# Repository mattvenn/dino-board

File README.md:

# DinoLight

A mosasaurus-shaped light-up circuit board: 20 side-firing addressable LEDs along the spine, a glowing
eye, capacitive touch pads on the bare front face, motion, compass, temperature, light and pressure sensors,
a buzzer, a rechargeable LiPo and USB-C.
The brain is an ESP32-S3 module intended to run CircuitPython. Designed in KiCad 10 for assembly by JLCPCB.

**Status:** work in progress. Read [NOTES.md](NOTES.md) first: it has the current state, every design
decision and its reason, the parts list with stock checks, the review findings, and the pin map.

## What is where

| Path | What it is |
|---|---|
| `NOTES.md` | The running record. Start here |
| `output/schematic.pdf` | The schematic to read (also `schematic_p1..4.png`) |
| `dinolight.kicad_sch`, `mcu.kicad_sch`, `leds.kicad_sch`, `sensors.kicad_sch` | The schematic, generated: do not edit by hand without reading the note below |
| `dinolight.kicad_pcb` | The board, generated from the schematic's netlist and routed by `tools/route_all.sh` |
| `tools/design_spec.py` | Every part and net, declared once. The source of truth |
| `tools/schematic.py` | Draws the schematic from the spec |
| `tools/build_board.py` | Builds the board: outline, placement, nets |
| `tools/route_all.sh` | Builds and routes the board start to finish (calls the tools below) |
| `tools/route_board.py` | Scripted tracks (LED strip, touch lines), autorouter hand-over, ground pours |
| `tools/patch_route.py`, `tools/trim_dangling.py` | Finish what the autorouter leaves open; tie in ground; tidy |
| `tools/freerouting_capped.sh` | Runs the Freerouting autorouter for a set number of passes |
| `routing/route_signals.ses` | The autorouter's last result, kept because it differs run to run |
| `outline/` | The outline generator and its SVG / PNG |
| `lib/` | Project symbols and footprints |
| `datasheets/` | Maker datasheets, named by JLCPCB part number |
| `draft/` | An early quote-only board and its JLCPCB upload files. Not for ordering |

## Regenerating

The schematic and board are written by scripts, so a change is made in `tools/` and the files are
regenerated. Anything edited by hand in KiCad is overwritten the next time a script runs.

```bash
export KICAD_DOCUMENTS_HOME="$PWD/kicad-user"
python3 tools/schematic.py export        # schematic files, PDF and PNGs, and build/sch/netlist.net
tools/route_all.sh                       # the board from that netlist, placed and routed: about 40 minutes
tools/route_all.sh finish                # the same, reusing the saved autorouter result
```

`tools/route_all.sh` needs KiCad 10, Java and Freerouting 2.1.0 at `~/.kicad-mcp/freerouting.jar`. Keep
the computer awake while it runs: the autorouter fails most connections if the machine sleeps part way.
The autorouter's result differs run to run, so check the board the script produces (its last lines
are KiCad's rule-check summary) instead of assuming it matches the last one.

`tools/schematic.py` needs `schdraw.py`, a small drawing library that is not in this repository yet;
`tools/design_spec.py` looks for it in `~/.claude/skills/pcb-for-assembly/scripts`. The board scripts
need KiCad's own Python (for `pcbnew`).

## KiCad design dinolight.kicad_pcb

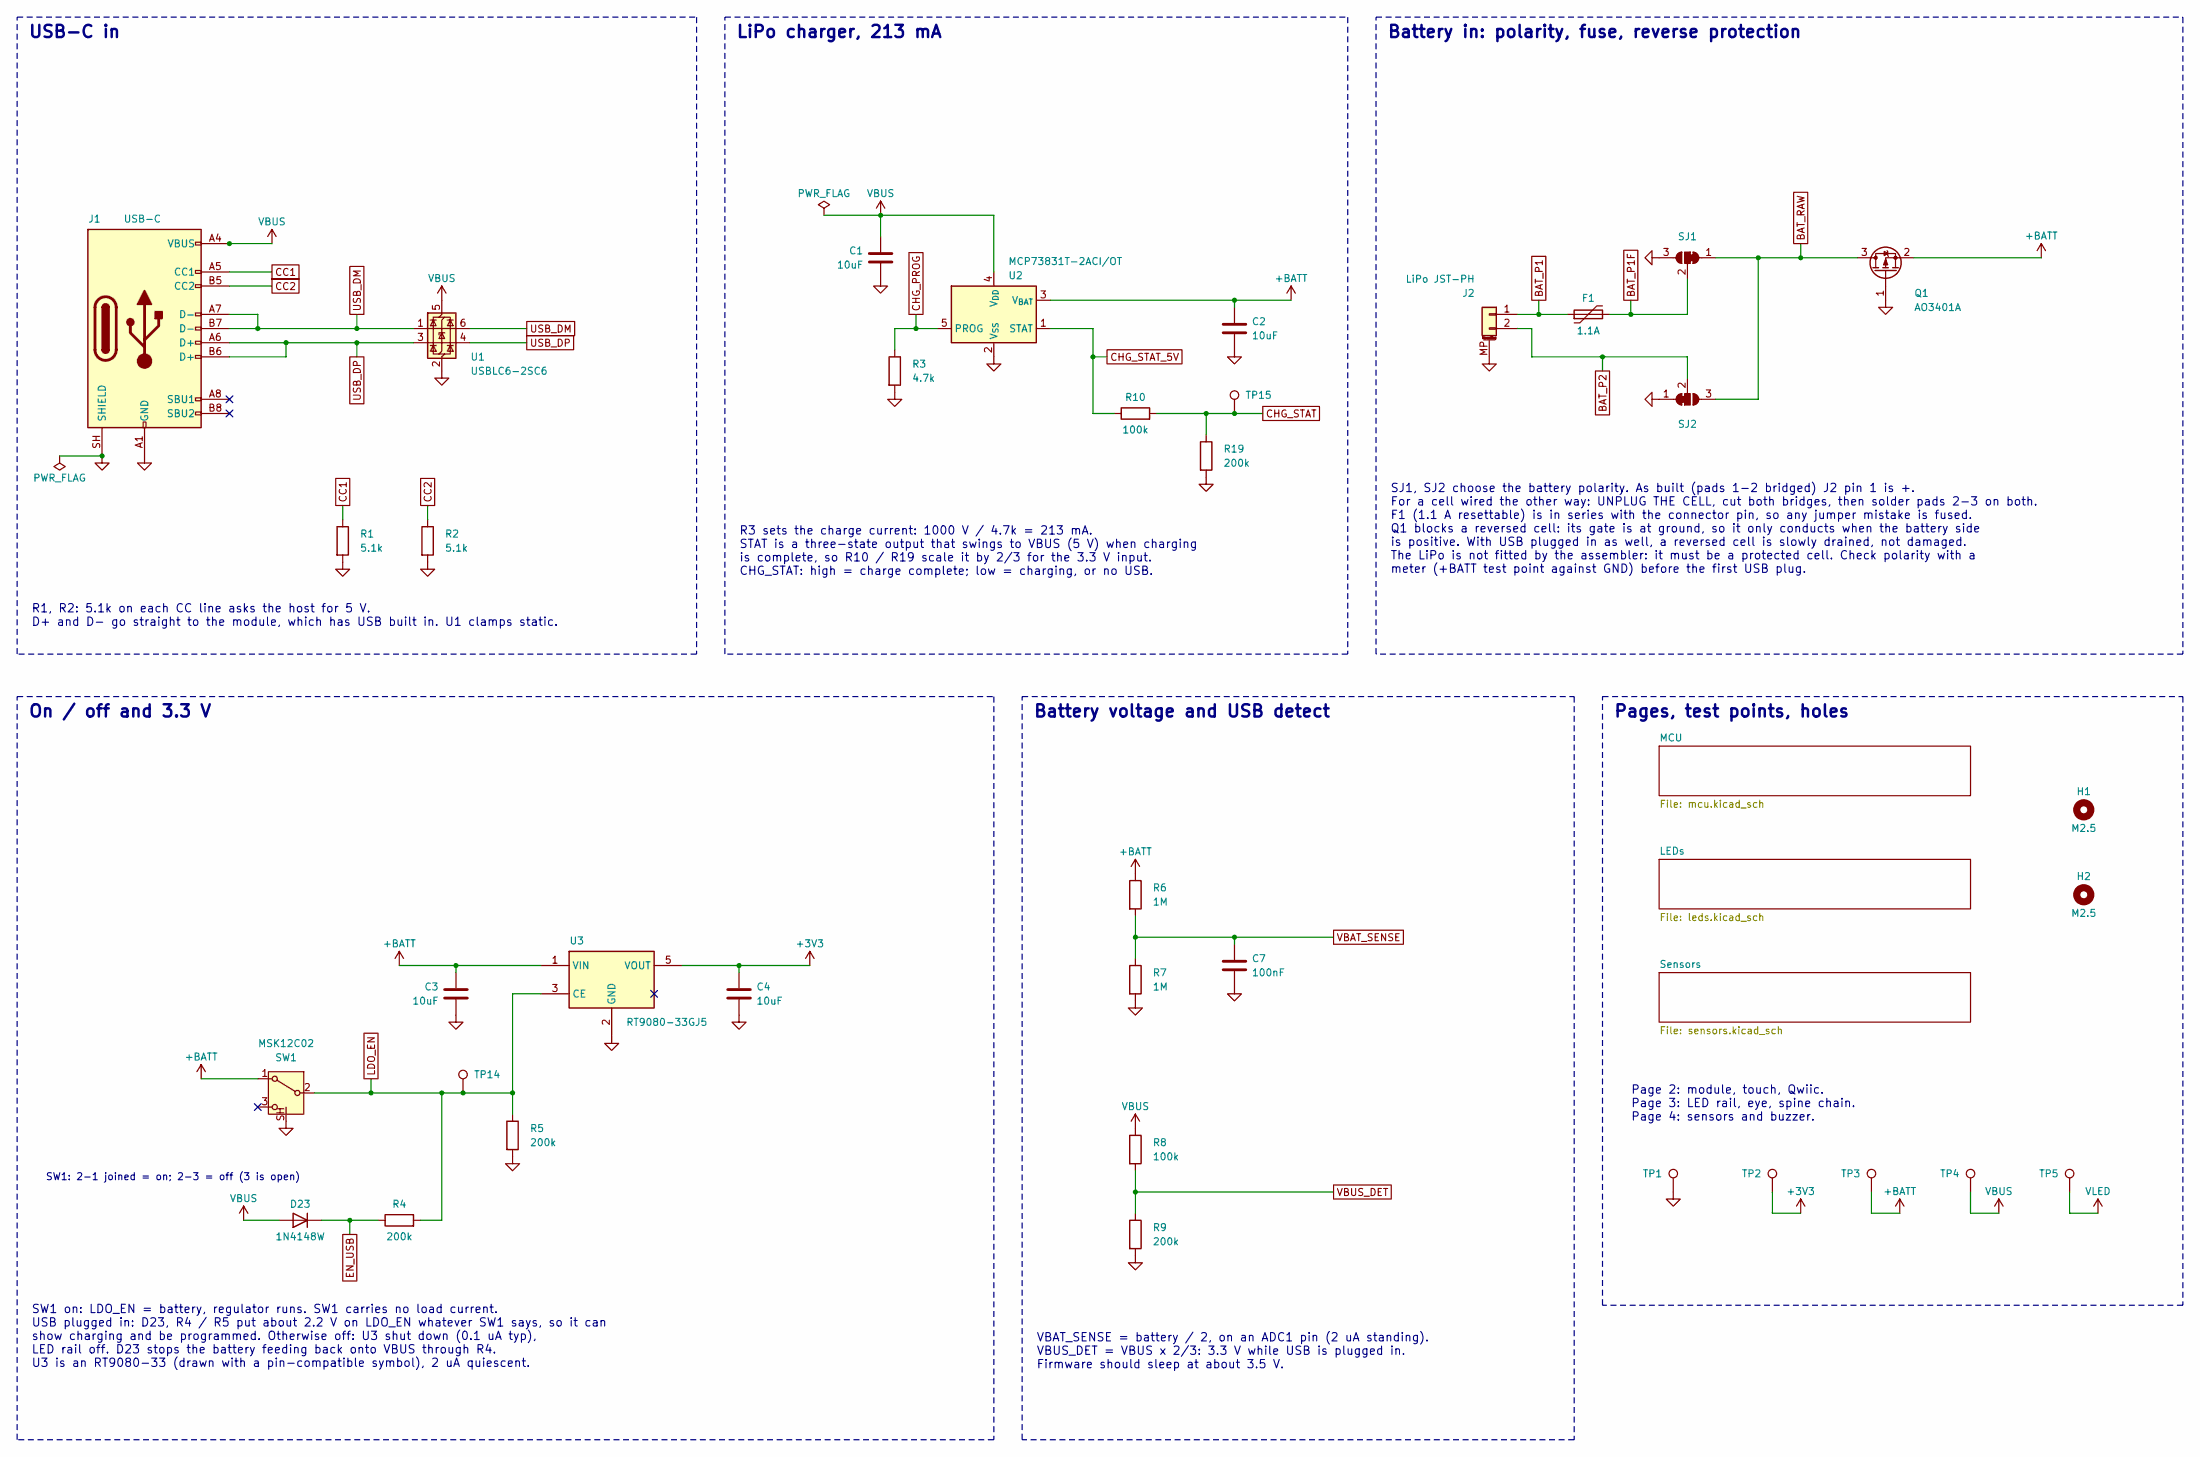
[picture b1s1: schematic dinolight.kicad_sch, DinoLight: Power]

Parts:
C1, C2, C3, C4: 10uF; C_0805_2012Metric; LCSC C15850
C7: 100nF; C_0402_1005Metric; LCSC C1525
D23: 1N4148W; D_SOD-123; LCSC C81598
F1: 1.1A; Fuse_1812_4532Metric; LCSC C21000
H1, H2: M2.5; MountingHole_2.7mm_M2.5
J1: USB-C; USB_C_Receptacle_HRO_TYPE-C-31-M-12; LCSC C165948
J2: LiPo JST-PH; JST_PH_S2B-PH-SM4-TB_1x02-1MP_P2.00mm_Horizontal; LCSC C295747
Q1: AO3401A; SOT-23; LCSC C15127
R1, R2: 5.1k; R_0402_1005Metric; LCSC C25905
R3: 4.7k; R_0402_1005Metric; LCSC C25900
R4, R5, R9, R19: 200k; R_0402_1005Metric; LCSC C25764
R6, R7: 1M; R_0402_1005Metric; LCSC C26083
R8, R10: 100k; R_0402_1005Metric; LCSC C25741
SJ1, SJ2: polarity; SolderJumper-3_P1.3mm_Bridged12_RoundedPad1.0x1.5mm
SW1: MSK12C02; SW_SPDT_Shouhan_MSK12C02; LCSC C431540
TP1: GND; TestPoint_Pad_D1.5mm
TP2: +3V3; TestPoint_Pad_D1.5mm
TP3: +BATT; TestPoint_Pad_D1.5mm
TP4: VBUS; TestPoint_Pad_D1.5mm
TP5: VLED; TestPoint_Pad_D1.5mm
TP14: LDO_EN; TestPoint_Pad_D1.5mm
TP15: CHG_STAT; TestPoint_Pad_D1.5mm
U1: USBLC6-2SC6; SOT-23-6; LCSC C7519
U2: MCP73831T-2ACI/OT; SOT-23-5; LCSC C424093
U3: RT9080-33GJ5; TSOT-23-5; LCSC C841192

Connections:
+3V3: C4.1, TP2.1, U3.5 (VOUT); also elsewhere on the board
+BATT: C2.1, C3.1, Q1.2 (S), R6.1, SW1.1 (A), TP3.1, U2.3 (V_{BAT}), U3.1 (VIN); also elsewhere on the board
BAT_P1: F1.1, J2.1
BAT_P1F: F1.2, SJ1.2 (C)
BAT_P2: J2.2, SJ2.2 (C)
BAT_RAW: Q1.3 (D), SJ1.1 (A), SJ2.3 (B)
CC1: J1.A5 (CC1), R1.1
CC2: J1.B5 (CC2), R2.1
CHG_PROG: R3.1, U2.5 (PROG)
CHG_STAT: R10.2, R19.1, TP15.1; also elsewhere on the board
CHG_STAT_5V: R10.1, U2.1 (STAT)
EN_USB: D23.1 (K), R4.1
GND: C1.2, C2.2, C3.2, C4.2, C7.2, J1.A1 (GND), J1.A12 (GND), J1.B1 (GND), J1.B12 (GND), J1.SH (SHIELD), J2.MP (MountPin), Q1.1 (G), R1.2, R2.2, R3.2, R5.2, R7.2, R9.2, R19.2, SJ1.3 (B), SJ2.1 (A), SW1.SH, TP1.1, U1.2 (GND), U2.2 (V_{SS}), U3.2 (GND); also elsewhere on the board
LDO_EN: R4.2, R5.1, SW1.2 (B), TP14.1, U3.3 (CE)
USB_DM: J1.A7 (D-), J1.B7 (D-), U1.1 (I/O1), U1.6 (I/O1); also elsewhere on the board
USB_DP: J1.A6 (D+), J1.B6 (D+), U1.3 (I/O2), U1.4 (I/O2); also elsewhere on the board
VBAT_SENSE: C7.1, R6.2, R7.1; also elsewhere on the board
VBUS: C1.1, D23.2 (A), J1.A4 (VBUS), J1.A9 (VBUS), J1.B4 (VBUS), J1.B9 (VBUS), R8.1, TP4.1, U1.5 (VBUS), U2.4 (V_{DD})
VBUS_DET: R8.2, R9.1; also elsewhere on the board
VLED: TP5.1; also elsewhere on the board

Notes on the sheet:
USB-C in
R1, R2: 5.1k on each CC line asks the host for 5 V. D+ and D- go straight to the module, which has USB built in. U1 clamps static.
LiPo charger, 213 mA
R3 sets the charge current: 1000 V / 4.7k = 213 mA. STAT is a three-state output that swings to VBUS (5 V) when charging is complete, so R10 / R19 scale it by 2/3 for the 3.3 V input. CHG_STAT: high = charge complete; low = charging, or no USB.
Battery in: polarity, fuse, reverse protection
SJ1, SJ2 choose the battery polarity. As built (pads 1-2 bridged) J2 pin 1 is +. For a cell wired the other way: UNPLUG THE CELL, cut both bridges, then solder pads 2-3 on both. F1 (1.1 A resettable) is in series with the connector pin, so any jumper mistake is fused. Q1 blocks a reversed cell: its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
On / off and 3.3 V
SW1: 2-1 joined = on; 2-3 = off (3 is open)
SW1 on: LDO_EN = battery, regulator runs. SW1 carries no load current. USB plugged in: D23, R4 / R5 put about 2.2 V on LDO_EN whatever SW1 says, so it can show charging and be programmed. Otherwise off: U3 shut down (0.1 uA typ), LED rail off. D23 stops the battery feeding back onto VBUS through R4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
Battery voltage and USB detect
VBAT_SENSE = battery / 2, on an ADC1 pin (2 uA standing). VBUS_DET = VBUS x 2/3: 3.3 V while USB is plugged in. Firmware should sleep at about 3.5 V.
Pages, test points, holes
Page 2: module, touch, Qwiic. Page 3: LED rail, eye, spine chain. Page 4: sensors and buzzer.

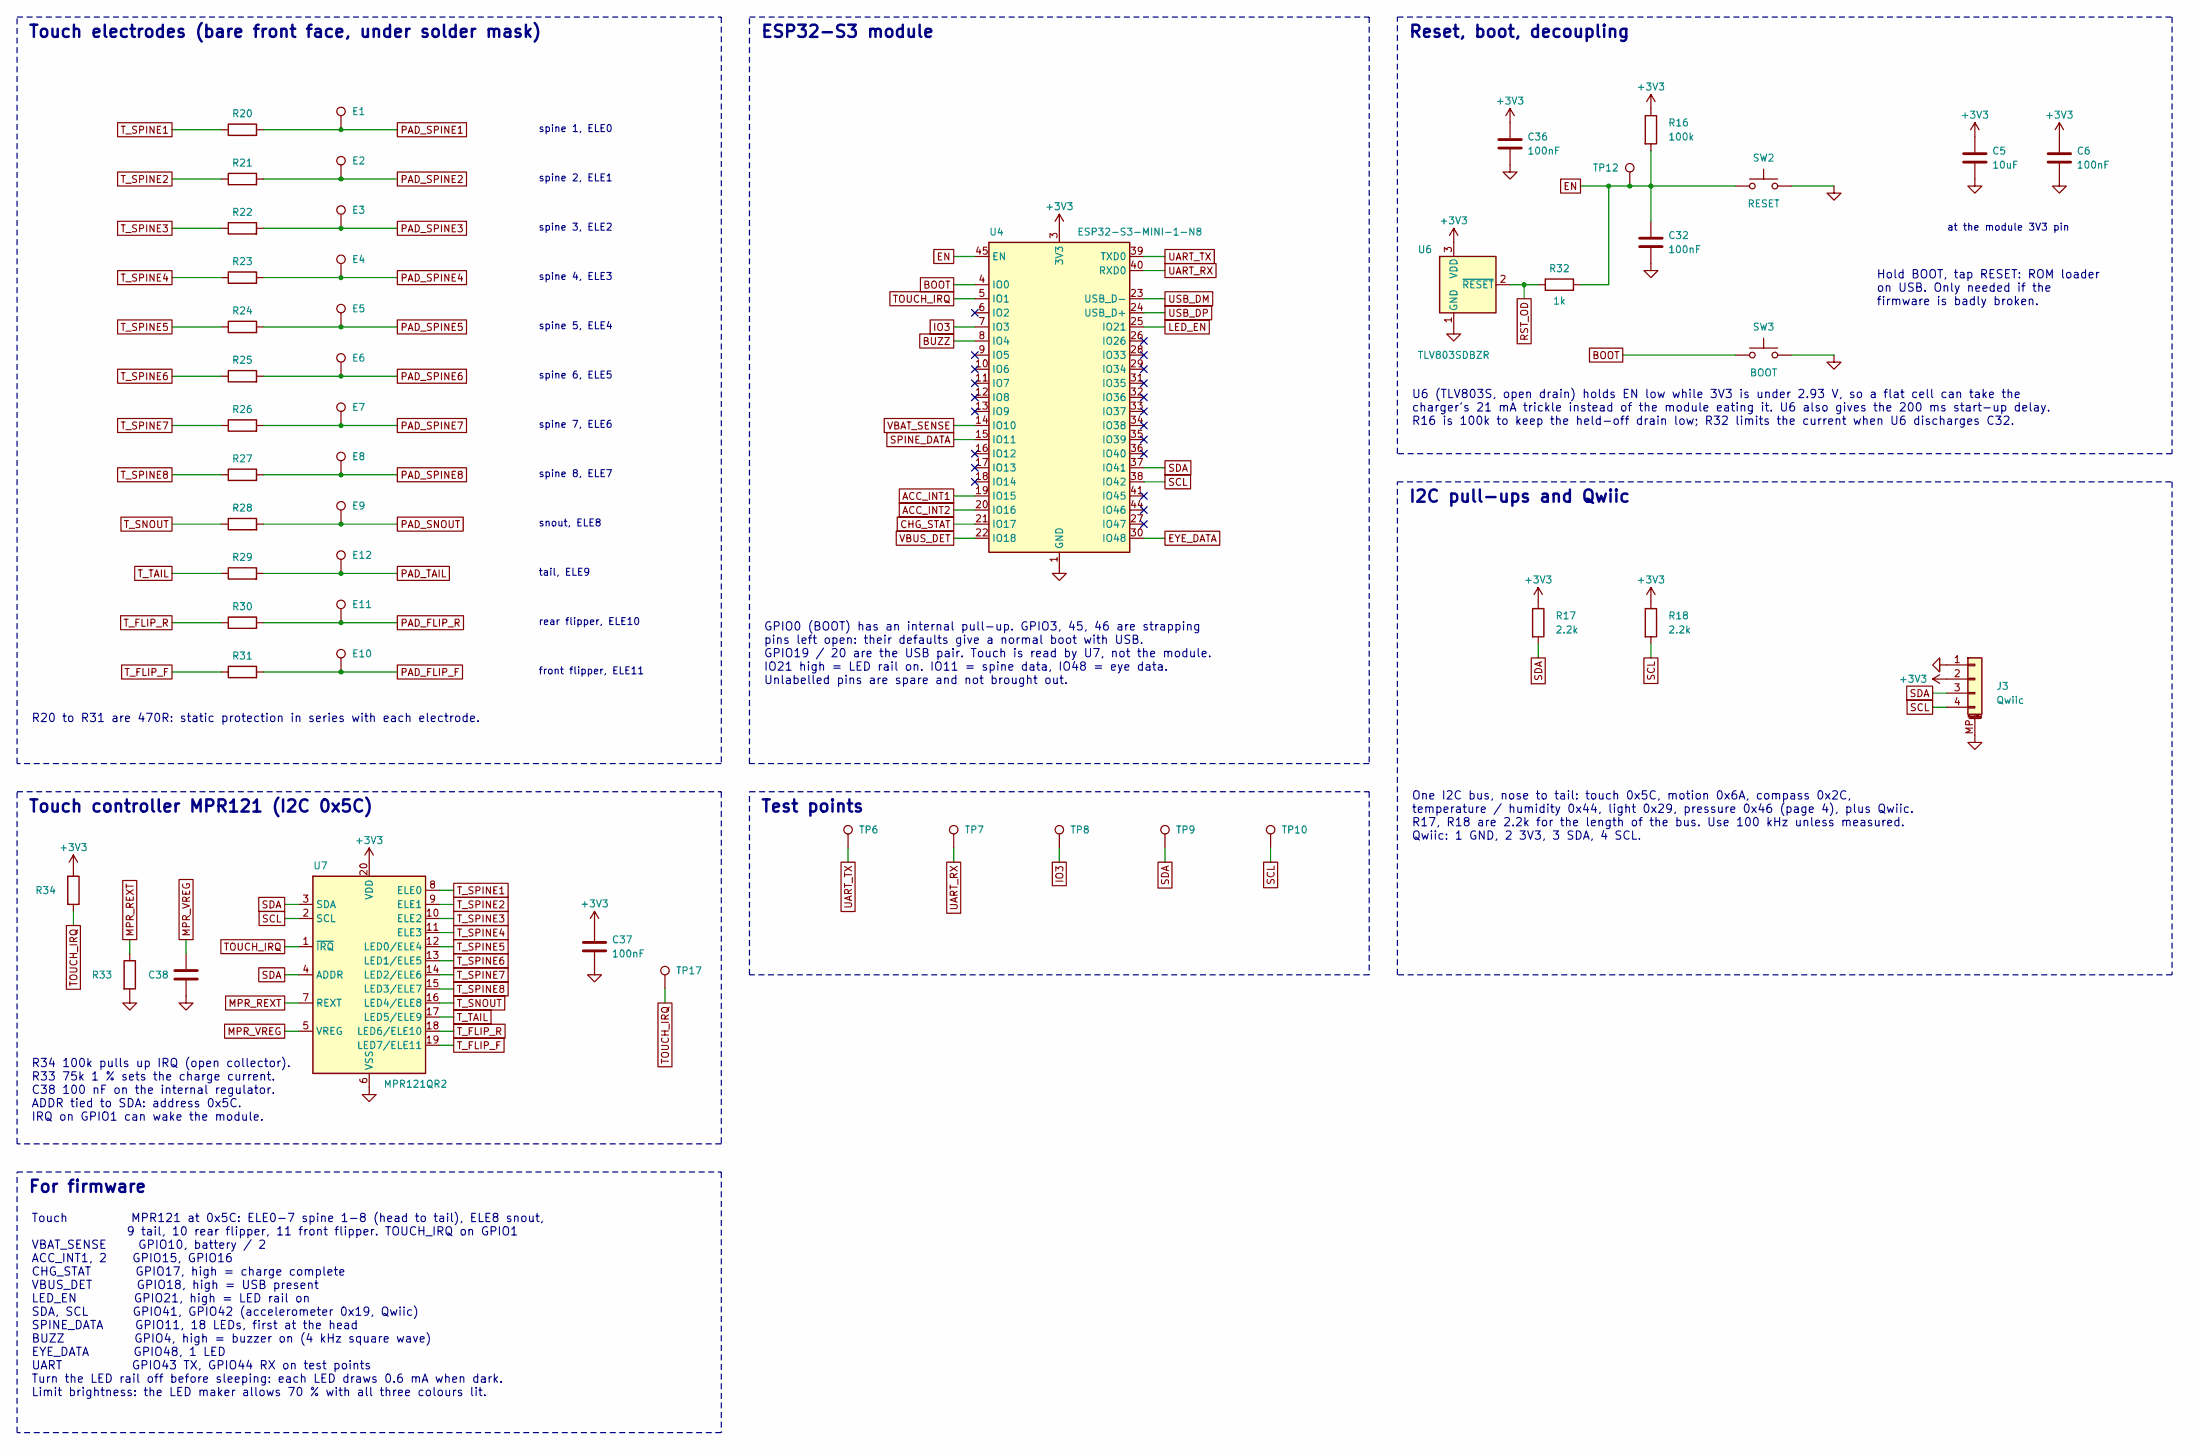
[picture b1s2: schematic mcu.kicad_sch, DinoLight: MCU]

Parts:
C5: 10uF; C_0805_2012Metric; LCSC C15850
C6, C32, C36, C37, C38: 100nF; C_0402_1005Metric; LCSC C1525
E1: spine 1; TouchAnchor
E2: spine 2; TouchAnchor
E3: spine 3; TouchAnchor
E4: spine 4; TouchAnchor
E5: spine 5; TouchAnchor
E6: spine 6; TouchAnchor
E7: spine 7; TouchAnchor
E8: spine 8; TouchAnchor
E9: snout; TouchAnchor
E10: front flipper; TouchAnchor
E11: rear flipper; TouchAnchor
E12: tail; TouchAnchor
J3: Qwiic; JST_SH_SM04B-SRSS-TB_1x04-1MP_P1.00mm_Horizontal; LCSC C160404
R16, R34: 100k; R_0402_1005Metric; LCSC C25741
R17, R18: 2.2k; R_0402_1005Metric; LCSC C25879
R20, R21, R22, R23, R24, R25, R26, R27, R28, R29, R30, R31: 470R; R_0402_1005Metric; LCSC C25117
R32: 1k; R_0402_1005Metric; LCSC C11702
R33: 75k 1%; R_0603_1608Metric; LCSC C23242
SW2: RESET; SW_Push_1P1T_XKB_TS-1187A; LCSC C318884
SW3: BOOT; SW_Push_1P1T_XKB_TS-1187A; LCSC C318884
TP6: UART_TX; TestPoint_Pad_D1.5mm
TP7: UART_RX; TestPoint_Pad_D1.5mm
TP8: IO3; TestPoint_Pad_D1.5mm
TP9: SDA; TestPoint_Pad_D1.5mm
TP10: SCL; TestPoint_Pad_D1.5mm
TP12: EN; TestPoint_Pad_D1.5mm
TP17: TOUCH_IRQ; TestPoint_Pad_D1.5mm
U4: ESP32-S3-MINI-1-N8; ESP32-S2-MINI-1; LCSC C2913206
U6: TLV803SDBZR; SOT-23; LCSC C132016
U7: MPR121QR2; UQFN-20_3x3mm_P0.4mm; LCSC C91322

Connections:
+3V3: C5.1, C6.1, C36.1, C37.1, J3.2, R16.1, R17.1, R18.1, R34.1, U4.3 (3V3), U6.3 (VDD), U7.20 (VDD); also elsewhere on the board
ACC_INT1: U4.19 (IO15); also elsewhere on the board
ACC_INT2: U4.20 (IO16); also elsewhere on the board
BOOT: SW3.1, U4.4 (IO0)
BUZZ: U4.8 (IO4); also elsewhere on the board
CHG_STAT: U4.21 (IO17); also elsewhere on the board
EN: C32.1, R16.2, R32.2, SW2.1, TP12.1, U4.45 (EN)
EYE_DATA: U4.30 (IO48); also elsewhere on the board
GND: C5.2, C6.2, C32.2, C36.2, C37.2, C38.2, J3.1, J3.MP (MountPin), R33.2, SW2.2, SW3.2, U4.1 (GND), U4.2 (GND), U4.42 (GND), U4.43 (GND), U4.46 (GND), U4.47 (GND), U4.48 (GND), U4.49 (GND), U4.50 (GND), U4.51 (GND), U4.52 (GND), U4.53 (GND), U4.54 (GND), U4.55 (GND), U4.56 (GND), U4.57 (GND), U4.58 (GND), U4.59 (GND), U4.60 (GND), U4.61 (GND), U4.62 (GND), U4.63 (GND), U4.64 (GND), U4.65 (GND), U6.1 (GND), U7.6 (VSS); also elsewhere on the board
IO3: TP8.1, U4.7 (IO3)
LED_EN: U4.25 (IO21); also elsewhere on the board
MPR_REXT: R33.1, U7.7 (REXT)
MPR_VREG: C38.1, U7.5 (VREG)
PAD_FLIP_F: E10.1, R31.2
PAD_FLIP_R: E11.1, R30.2
PAD_SNOUT: E9.1, R28.2
PAD_SPINE1: E1.1, R20.2
PAD_SPINE2: E2.1, R21.2
PAD_SPINE3: E3.1, R22.2
PAD_SPINE4: E4.1, R23.2
PAD_SPINE5: E5.1, R24.2
PAD_SPINE6: E6.1, R25.2
PAD_SPINE7: E7.1, R26.2
PAD_SPINE8: E8.1, R27.2
PAD_TAIL: E12.1, R29.2
RST_OD: R32.1, U6.2 (~RESET)
SCL: J3.4, R18.2, TP10.1, U4.38 (IO42), U7.2 (SCL); also elsewhere on the board
SDA: J3.3, R17.2, TP9.1, U4.37 (IO41), U7.3 (SDA), U7.4 (ADDR); also elsewhere on the board
SPINE_DATA: U4.15 (IO11); also elsewhere on the board
TOUCH_IRQ: R34.2, TP17.1, U4.5 (IO1), U7.1 (~IRQ)
T_FLIP_F: R31.1, U7.19 (LED7/ELE11)
T_FLIP_R: R30.1, U7.18 (LED6/ELE10)
T_SNOUT: R28.1, U7.16 (LED4/ELE8)
T_SPINE1: R20.1, U7.8 (ELE0)
T_SPINE2: R21.1, U7.9 (ELE1)
T_SPINE3: R22.1, U7.10 (ELE2)
T_SPINE4: R23.1, U7.11 (ELE3)
T_SPINE5: R24.1, U7.12 (LED0/ELE4)
T_SPINE6: R25.1, U7.13 (LED1/ELE5)
T_SPINE7: R26.1, U7.14 (LED2/ELE6)
T_SPINE8: R27.1, U7.15 (LED3/ELE7)
T_TAIL: R29.1, U7.17 (LED5/ELE9)
UART_RX: TP7.1, U4.40 (RXD0)
UART_TX: TP6.1, U4.39 (TXD0)
USB_DM: U4.23 (USB_D-); also elsewhere on the board
USB_DP: U4.24 (USB_D+); also elsewhere on the board
VBAT_SENSE: U4.14 (IO10); also elsewhere on the board
VBUS_DET: U4.22 (IO18); also elsewhere on the board

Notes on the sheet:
Touch electrodes (bare front face, under solder mask)
spine 1, ELE0
spine 2, ELE1
spine 3, ELE2
spine 4, ELE3
spine 5, ELE4
spine 6, ELE5
spine 7, ELE6
spine 8, ELE7
snout, ELE8
tail, ELE9
rear flipper, ELE10
front flipper, ELE11
R20 to R31 are 470R: static protection in series with each electrode.
Touch controller MPR121 (I2C 0x5C)
R34 100k pulls up IRQ (open collector). R33 75k 1 % sets the charge current. C38 100 nF on the internal regulator. ADDR tied to SDA: address 0x5C. IRQ on GPIO1 can wake the module.
ESP32-S3 module
GPIO0 (BOOT) has an internal pull-up. GPIO3, 45, 46 are strapping pins left open: their defaults give a normal boot with USB. GPIO19 / 20 are the USB pair. Touch is read by U7, not the module. IO21 high = LED rail on. IO11 = spine data, IO48 = eye data. Unlabelled pins are spare and not brought out.
Reset, boot, decoupling
at the module 3V3 pin
Hold BOOT, tap RESET: ROM loader on USB. Only needed if the firmware is badly broken.
U6 (TLV803S, open drain) holds EN low while 3V3 is under 2.93 V, so a flat cell can take the charger's 21 mA trickle instead of the module eating it. U6 also gives the 200 ms start-up delay. R16 is 100k to keep the held-off drain low; R32 limits the current when U6 discharges C32.
I2C pull-ups and Qwiic
One I2C bus, nose to tail: touch 0x5C, motion 0x6A, compass 0x2C, temperature / humidity 0x44, light 0x29, pressure 0x46 (page 4), plus Qwiic. R17, R18 are 2.2k for the length of the bus. Use 100 kHz unless measured. Qwiic: 1 GND, 2 3V3, 3 SDA, 4 SCL.
Test points
For firmware
Touch MPR121 at 0x5C: ELE0-7 spine 1-8 (head to tail), ELE8 snout, 9 tail, 10 rear flipper, 11 front flipper. TOUCH_IRQ on GPIO1 VBAT_SENSE GPIO10, battery / 2 ACC_INT1, 2 GPIO15, GPIO16 CHG_STAT GPIO17, high = charge complete VBUS_DET GPIO18, high = USB present LED_EN GPIO21, high = LED rail on SD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

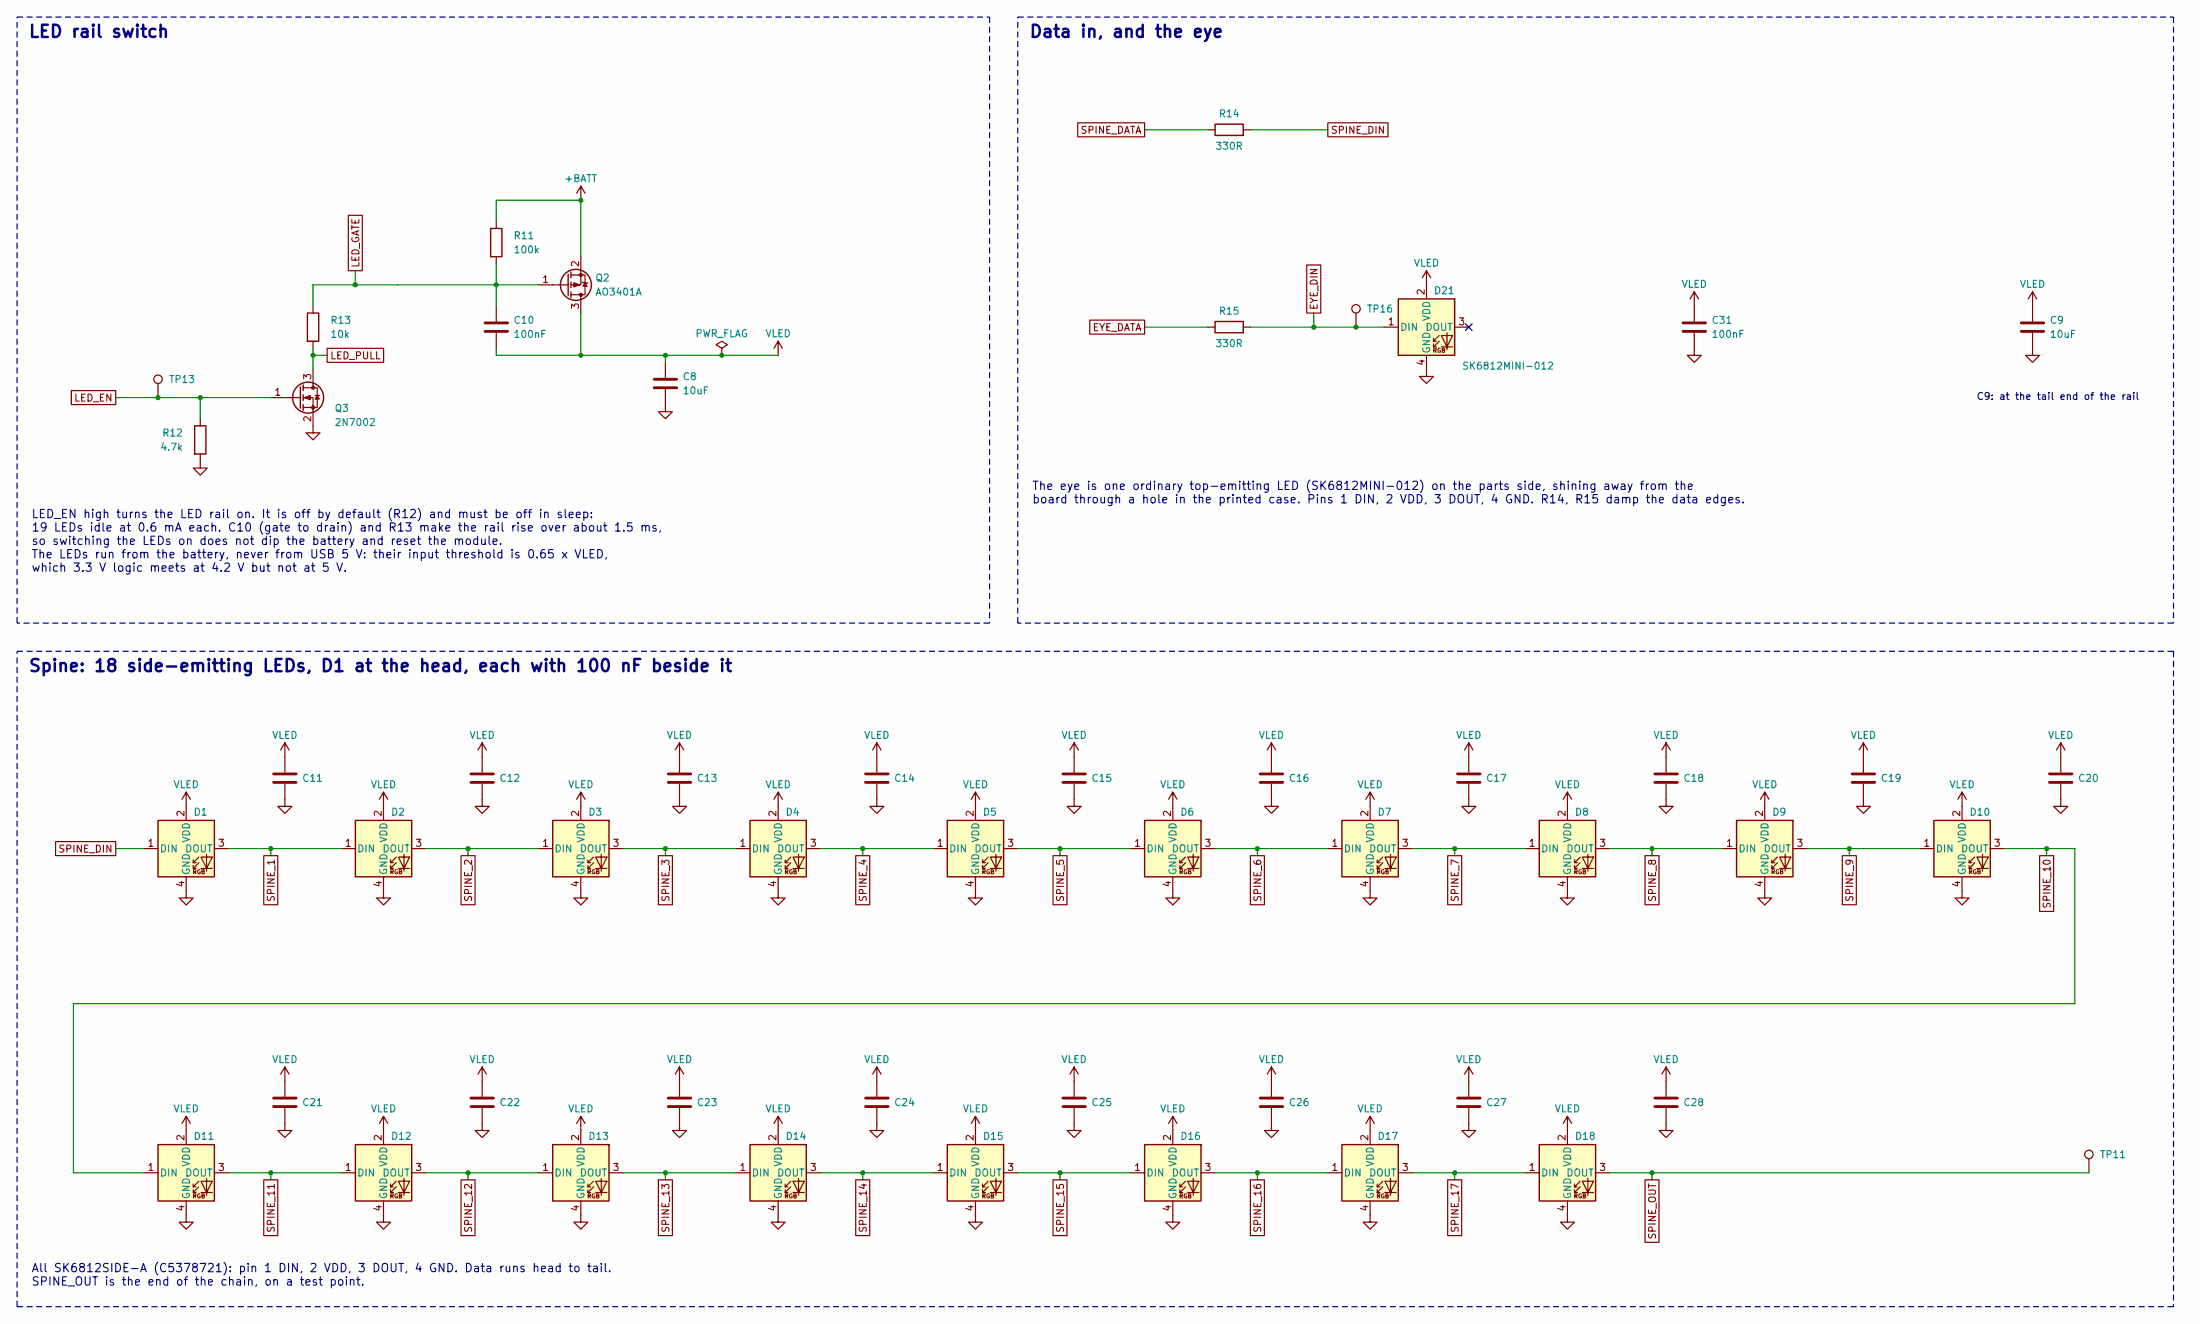
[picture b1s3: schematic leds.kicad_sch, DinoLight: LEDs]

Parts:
C8, C9: 10uF; C_0805_2012Metric; LCSC C15850
C10, C11, C12, C13, C14, C15, C16, C17, C18, C19, C20, C21, C22, C23, C24, C25, C26, C27, C28, C31: 100nF; C_0402_1005Metric; LCSC C1525
D1, D2, D3, D4, D5, D6, D7, D8, D9, D10, D11, D12, D13, D14, D15, D16, D17, D18: SK6812SIDE-A; LED_SK6812SIDE-A_4.0x1.6mm; LCSC C5378721
D21: SK6812MINI-012; LED_SK6812MINI-012_3.7x3.5mm; LCSC C2886570
Q2: AO3401A; SOT-23; LCSC C15127
Q3: 2N7002; SOT-23; LCSC C8545
R11: 100k; R_0402_1005Metric; LCSC C25741
R12: 4.7k; R_0402_1005Metric; LCSC C25900
R13: 10k; R_0402_1005Metric; LCSC C25744
R14, R15: 330R; R_0402_1005Metric; LCSC C25104
TP11: SPINE_OUT; TestPoint_Pad_D1.5mm
TP13: LED_EN; TestPoint_Pad_D1.5mm
TP16: EYE_DIN; TestPoint_Pad_D1.5mm

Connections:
+BATT: Q2.2 (S), R11.1; also elsewhere on the board
EYE_DATA: R15.1; also elsewhere on the board
EYE_DIN: D21.1 (DIN), R15.2, TP16.1
GND: C8.2, C9.2, C11.2, C12.2, C13.2, C14.2, C15.2, C16.2, C17.2, C18.2, C19.2, C20.2, C21.2, C22.2, C23.2, C24.2, C25.2, C26.2, C27.2, C28.2, C31.2, D1.4 (GND), D2.4 (GND), D3.4 (GND), D4.4 (GND), D5.4 (GND), D6.4 (GND), D7.4 (GND), D8.4 (GND), D9.4 (GND), D10.4 (GND), D11.4 (GND), D12.4 (GND), D13.4 (GND), D14.4 (GND), D15.4 (GND), D16.4 (GND), D17.4 (GND), D18.4 (GND), D21.4 (GND), Q3.2 (S), R12.2; also elsewhere on the board
LED_EN: Q3.1 (G), R12.1, TP13.1; also elsewhere on the board
LED_GATE: C10.1, Q2.1 (G), R11.2, R13.1
LED_PULL: Q3.3 (D), R13.2
SPINE_1: D1.3 (DOUT), D2.1 (DIN)
SPINE_2: D2.3 (DOUT), D3.1 (DIN)
SPINE_3: D3.3 (DOUT), D4.1 (DIN)
SPINE_4: D4.3 (DOUT), D5.1 (DIN)
SPINE_5: D5.3 (DOUT), D6.1 (DIN)
SPINE_6: D6.3 (DOUT), D7.1 (DIN)
SPINE_7: D7.3 (DOUT), D8.1 (DIN)
SPINE_8: D8.3 (DOUT), D9.1 (DIN)
SPINE_9: D9.3 (DOUT), D10.1 (DIN)
SPINE_10: D10.3 (DOUT), D11.1 (DIN)
SPINE_11: D11.3 (DOUT), D12.1 (DIN)
SPINE_12: D12.3 (DOUT), D13.1 (DIN)
SPINE_13: D13.3 (DOUT), D14.1 (DIN)
SPINE_14: D14.3 (DOUT), D15.1 (DIN)
SPINE_15: D15.3 (DOUT), D16.1 (DIN)
SPINE_16: D16.3 (DOUT), D17.1 (DIN)
SPINE_17: D17.3 (DOUT), D18.1 (DIN)
SPINE_DATA: R14.1; also elsewhere on the board
SPINE_DIN: D1.1 (DIN), R14.2
SPINE_OUT: D18.3 (DOUT), TP11.1
VLED: C8.1, C9.1, C10.2, C11.1, C12.1, C13.1, C14.1, C15.1, C16.1, C17.1, C18.1, C19.1, C20.1, C21.1, C22.1, C23.1, C24.1, C25.1, C26.1, C27.1, C28.1, C31.1, D1.2 (VDD), D2.2 (VDD), D3.2 (VDD), D4.2 (VDD), D5.2 (VDD), D6.2 (VDD), D7.2 (VDD), D8.2 (VDD), D9.2 (VDD), D10.2 (VDD), D11.2 (VDD), D12.2 (VDD), D13.2 (VDD), D14.2 (VDD), D15.2 (VDD), D16.2 (VDD), D17.2 (VDD), D18.2 (VDD), D21.2 (VDD), Q2.3 (D); also elsewhere on the board

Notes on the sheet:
LED rail switch
LED_EN high turns the LED rail on. It is off by default (R12) and must be off in sleep: 19 LEDs idle at 0.6 mA each. C10 (gate to drain) and R13 make the rail rise over about 1.5 ms, so switching the LEDs on does not dip the battery and reset the module. The LEDs run from the battery, never from US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
Data in, and the eye
C9: at the tail end of the rail
The eye is one ordinary top-emitting LED (SK6812MINI-012) on the parts side, shining away from the board through a hole in the printed case. Pins 1 DIN, 2 VDD, 3 DOUT, 4 GND. R14, R15 damp the data edges.
Spine: 18 side-emitting LEDs, D1 at the head, each with 100 nF beside it
All SK6812SIDE-A (C5378721): pin 1 DIN, 2 VDD, 3 DOUT, 4 GND. Data runs head to tail. SPINE_OUT is the end of the chain, on a test point.

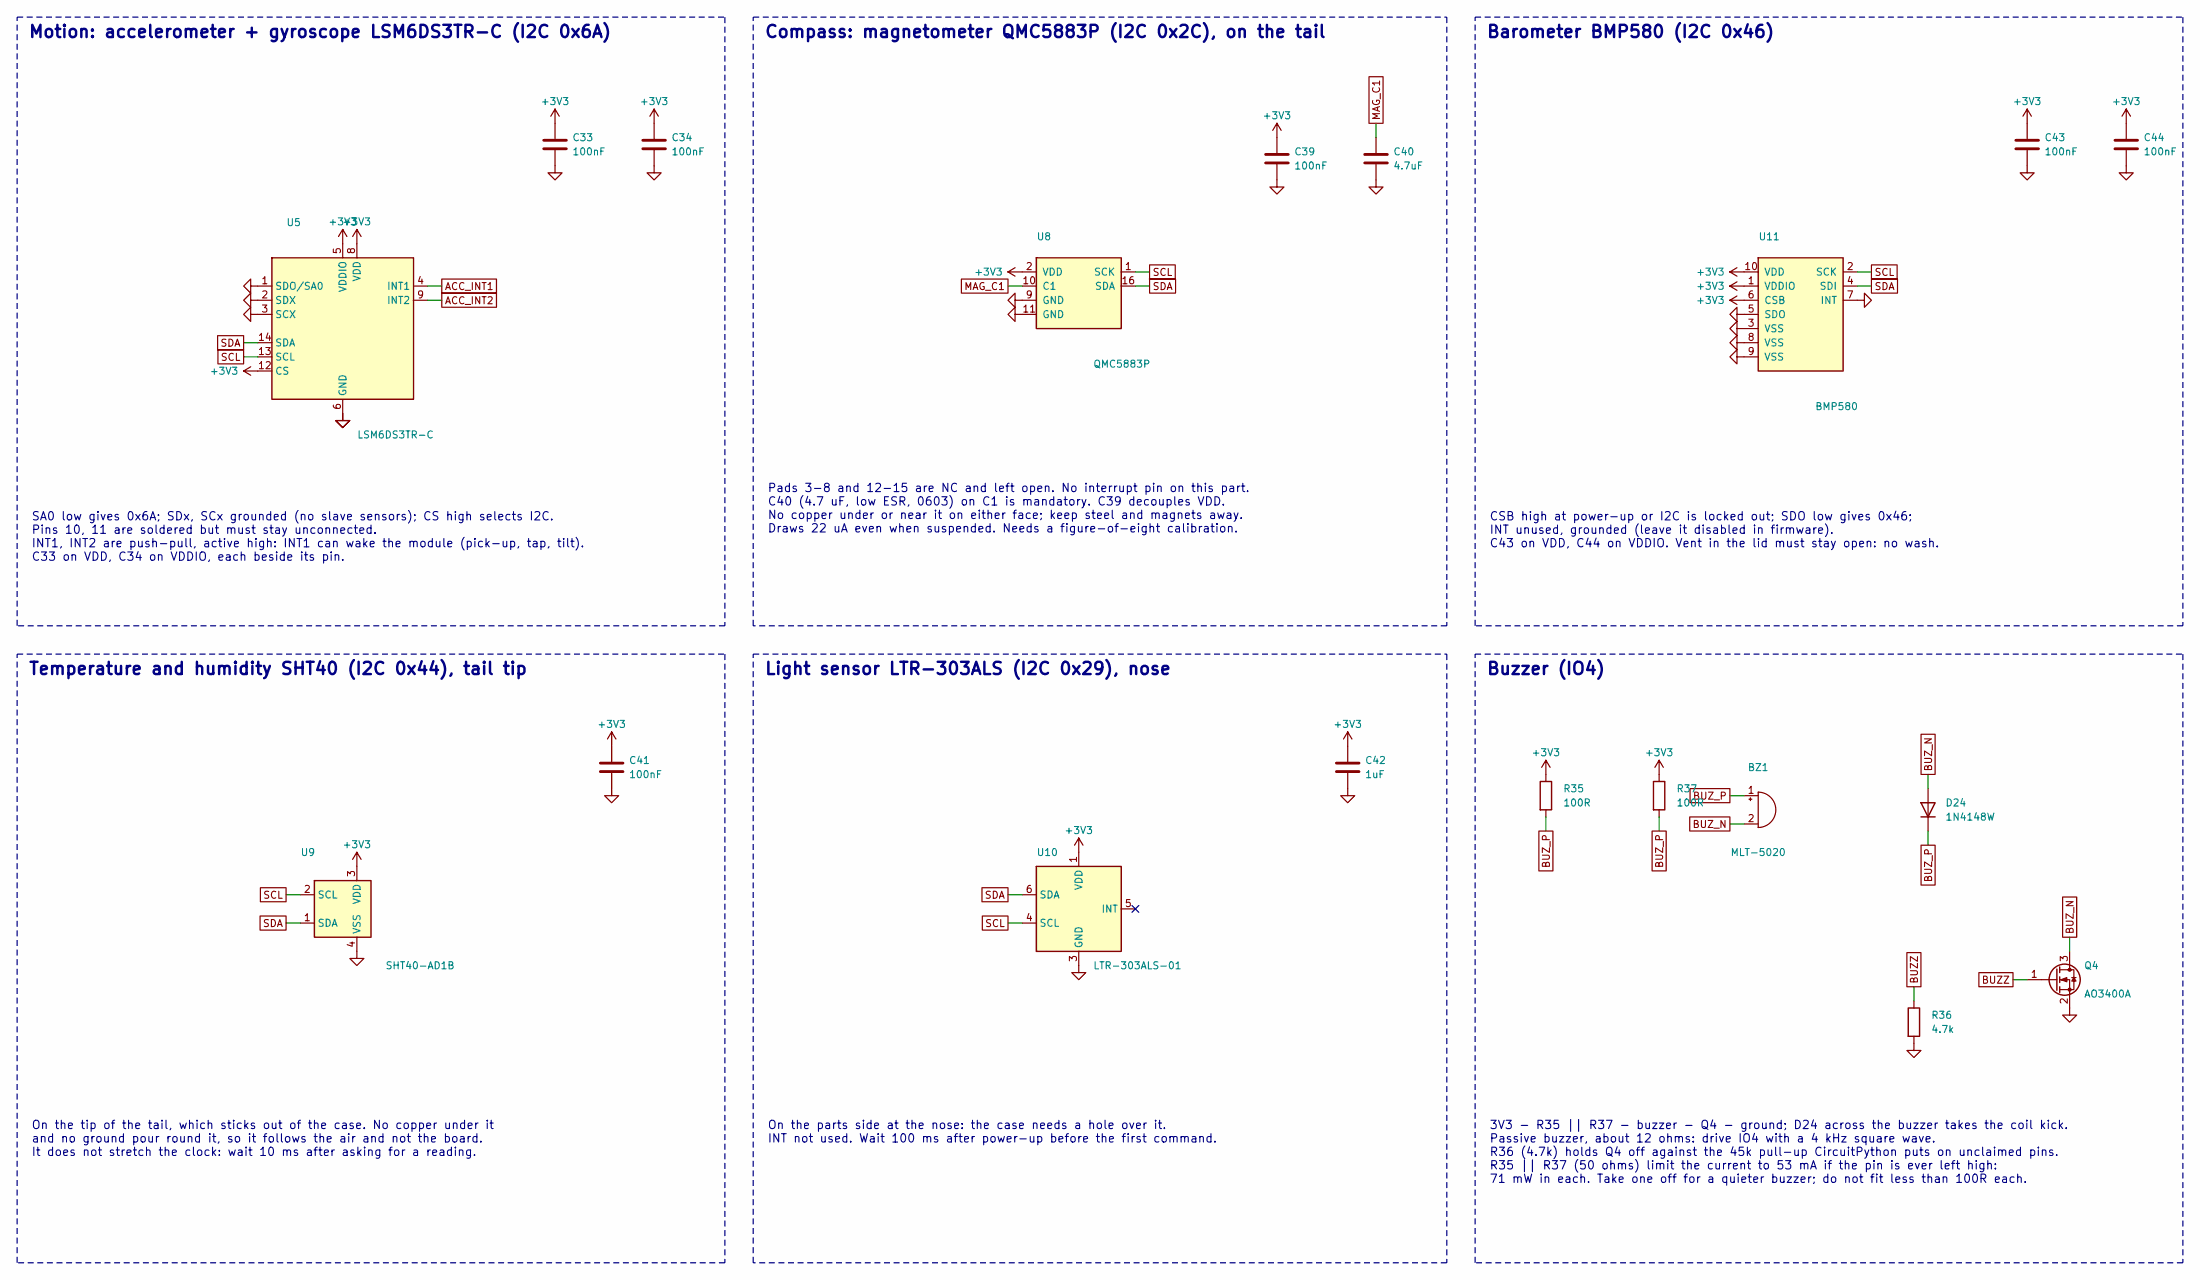
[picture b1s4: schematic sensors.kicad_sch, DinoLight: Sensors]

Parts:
BZ1: MLT-5020; Buzzer_MLT-5020; LCSC C94598
C33, C34, C39, C41, C43, C44: 100nF; C_0402_1005Metric; LCSC C1525
C40: 4.7uF; C_0603_1608Metric; LCSC C19666
C42: 1uF; C_0402_1005Metric; LCSC C52923
D24: 1N4148W; D_SOD-123; LCSC C81598
Q4: AO3400A; SOT-23; LCSC C20917
R35, R37: 100R; R_0805_2012Metric; LCSC C17408
R36: 4.7k; R_0402_1005Metric; LCSC C25900
U5: LSM6DS3TR-C; LGA-14_3x2.5mm_P0.5mm_LayoutBorder3x4y; LCSC C967633
U8: QMC5883P; LGA-16_3x3mm_P0.5mm; LCSC C2847467
U9: SHT40-AD1B; Sensirion_DFN-4_1.5x1.5mm_P0.8mm_SHT4x_NoCentralPad; LCSC C2909890
U10: LTR-303ALS-01; Lite-On_LTR-303ALS-01; LCSC C364577
U11: BMP580; Bosch_LGA-10_2x2mm_P0.5mm_BMP580; LCSC C22391138

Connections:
+3V3: C33.1, C34.1, C39.1, C41.1, C42.1, C43.1, C44.1, R35.1, R37.1, U5.5 (VDDIO), U5.8 (VDD), U5.12 (CS), U8.2 (VDD), U9.3 (VDD), U10.1 (VDD), U11.1 (VDDIO), U11.6 (CSB), U11.10 (VDD); also elsewhere on the board
ACC_INT1: U5.4 (INT1); also elsewhere on the board
ACC_INT2: U5.9 (INT2); also elsewhere on the board
BUZZ: Q4.1 (G), R36.1; also elsewhere on the board
BUZ_N: BZ1.2 (-), D24.2 (A), Q4.3 (D)
BUZ_P: BZ1.1 (+), D24.1 (K), R35.2, R37.2
GND: C33.2, C34.2, C39.2, C40.2, C41.2, C42.2, C43.2, C44.2, Q4.2 (S), R36.2, U5.1 (SDO/SA0), U5.2 (SDX), U5.3 (SCX), U5.6 (GND), U5.7 (GND), U8.9 (GND), U8.11 (GND), U9.4 (VSS), U10.3 (GND), U11.3 (VSS), U11.5 (SDO), U11.7 (INT), U11.8 (VSS), U11.9 (VSS); also elsewhere on the board
MAG_C1: C40.1, U8.10 (C1)
SCL: U5.13 (SCL), U8.1 (SCK), U9.2 (SCL), U10.4 (SCL), U11.2 (SCK); also elsewhere on the board
SDA: U5.14 (SDA), U8.16 (SDA), U9.1 (SDA), U10.6 (SDA), U11.4 (SDI); also elsewhere on the board

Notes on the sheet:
Motion: accelerometer + gyroscope LSM6DS3TR-C (I2C 0x6A)
SA0 low gives 0x6A; SDx, SCx grounded (no slave sensors); CS high selects I2C. Pins 10, 11 are soldered but must stay unconnected. INT1, INT2 are push-pull, active high: INT1 can wake the module (pick-up, tap, tilt). C33 on VDD, C34 on VDDIO, each beside its pin.
Compass: magnetometer QMC5883P (I2C 0x2C), on the tail
Pads 3-8 and 12-15 are NC and left open. No interrupt pin on this part. C40 (4.7 uF, low ESR, 0603) on C1 is mandatory. C39 decouples VDD. No copper under or near it on either face; keep steel and magnets away. Draws 22 uA even when suspended. Needs a figure-of-eight calibration.
Barometer BMP580 (I2C 0x46)
CSB high at power-up or I2C is locked out; SDO low gives 0x46; INT unused, grounded (leave it disabled in firmware). C43 on VDD, C44 on VDDIO. Vent in the lid must stay open: no wash.
Temperature and humidity SHT40 (I2C 0x44), tail tip
On the tip of the tail, which sticks out of the case. No copper under it and no ground pour round it, so it follows the air and not the board. It does not stretch the clock: wait 10 ms after asking for a reading.
Light sensor LTR-303ALS (I2C 0x29), nose
On the parts side at the nose: the case needs a hole over it. INT not used. Wait 100 ms after power-up before the first command.
Buzzer (IO4)
3V3 - R35 || R37 - buzzer - Q4 - ground; D24 across the buzzer takes the coil kick. Passive buzzer, about 12 ohms: drive IO4 with a 4 kHz square wave. R36 (4.7k) holds Q4 off against the 45k pull-up CircuitPython puts on unclaimed pins. R35 || R37 (50 ohms) limit the current to 53 mA if the pin is 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

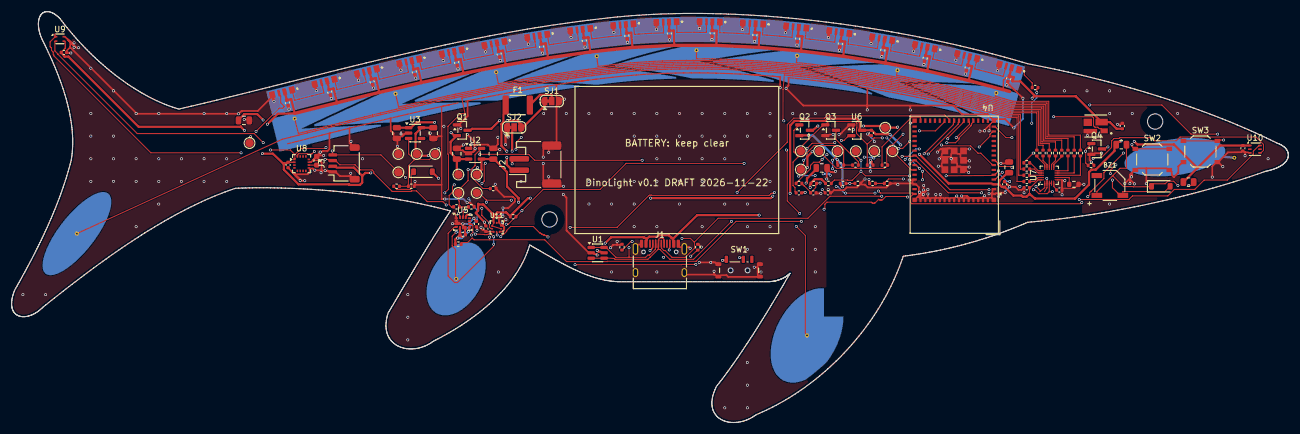
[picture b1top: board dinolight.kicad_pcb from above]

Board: 4 copper layers, 225.6 x 72.6 mm, 155 parts (0 on the bottom side), 86 nets.

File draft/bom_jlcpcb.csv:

Comment,Designator,Footprint,LCSC Part #
10uF,"C1,C2,C5,C8,C9,C34",C_0805_2012Metric,C15850
1uF,"C3,C4,C32",C_0402_1005Metric,C52923
100nF,"C6,C7,C10,C11,C12,C13,C14,C15,C16,C17,C18,C19,C20,C21,C22,C23,C24,C25,C26,C27,C28,C29,C30,C31,C33",C_0402_1005Metric,C1525
SK6812SIDE-A,"D1,D2,D3,D4,D5,D6,D7,D8,D9,D10,D11,D12,D13,D14,D15,D16,D17,D18,D19,D20",LED_SK6812SIDE-A_4.0x1.6mm,C5378721
SK6812MINI-E,D21,LED_SK6812MINI-E_3.2x2.8mm_P1.5mm_ReverseMount,C5149201
PTC 1.1A,F1,Fuse_1812_4532Metric,C21000
USB-C 16P,J1,USB_C_Receptacle_HRO_TYPE-C-31-M-12,C165948
JST-PH 2P,J2,JST_PH_S2B-PH-SM4-TB_1x02-1MP_P2.00mm_Horizontal,C295747
Qwiic,J3,JST_SH_SM04B-SRSS-TB_1x04-1MP_P1.00mm_Horizontal,C160404
AO3401A,"Q1,Q2",SOT-23,C15127
2N7002,Q3,SOT-23,C8545
5.1k,"R1,R2",R_0402_1005Metric,C25905
4.7k,"R3,R17,R18",R_0402_1005Metric,C25900
100k,"R4,R5,R8,R9,R11,R12",R_0402_1005Metric,C25741
1M,"R6,R7",R_0402_1005Metric,C26083
10k,"R10,R13,R16",R_0402_1005Metric,C25744
330R,"R14,R15",R_0402_1005Metric,C25104
MSK12C02,SW1,SW_SPDT_Shouhan_MSK12C02,C431540
TS-1187A-B-A-B,"SW2,SW3",SW_Push_1P1T_XKB_TS-1187A,C318884
USBLC6-2SC6,U1,SOT-23-6,C7519
MCP73831T-2ACI/OT,U2,SOT-23-5,C424093
RT9080-33GJ5,U3,TSOT-23-5,C841192
ESP32-S3-MINI-1-N8,U4,ESP32-S2-MINI-1,C2913206
LIS2DH12TR,U5,LGA-12_2x2mm_P0.5mm,C110926
